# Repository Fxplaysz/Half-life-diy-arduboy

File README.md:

# Half-life-diy-arduboy
Hello everyone, this is my repository for my diy arduboy. Here you'll find the pcb and the 3d models later on.
I have made this DIY arduboy because i like mini handheld game consoles and electronics. This DIY Arduboy is very easy to build and can be made by anyone easily.

Aruduboy is a open source game console made by Kevin Bates. He has opensourced his console and made it easier for anyone to build it and have fun with it. I remember a few years back i tried making it by myself but i failed in doing so because of the technicalities in building it. So i've decided to make this project to let anyone make a DIY Arduboy easily and have fun while doing it.

It was made using KiCad and with the help of the internet. 
I made it in 2 days in the span of 5 hours in the 2 days.

# Features
* 0.96 SPI OLED display
* ISP pins for easy programming
* Buzzer for audio
* Flash chip to store more then 500+ games
* RGB LED
* *Silent* SMD push button switches. Good for long term gaming.

# Instructions
* Flash [Arduboy bootloader](https://github.com/MrBlinky/Arduboy-homemade-package) using the ISP header and a [usb asp](https://robu.in/product/usbasp-avr-programming-device-for-atmel-proccessors/)
* Upload games using the cart builder from MrBlinky [Arduboy-Python-Utilities](https://github.com/MrBlinky/Arduboy-Python-Utilities)
* Start Playing with it!

  - *More detailed instructions will be uploaded later*
    
# Photos
These are some of the photos of my PCBs.
1) PCB with smd mounted flash chip.
- Front

<details>
  <summary>Click to view front with components</summary>
  
</details>

- Back

<details>
  <summary>Click to view back with components</summary>
  
</details>

* PCB Lay out

2) PCB with support for flash module.
- Front

<details>
  <summary>Click to view front with components</summary>
  
</details>

- Back

<details>
  <summary>Click to view back with components</summary>

</details>

* PCB Lay out

* Schematics
   - [DIY Arduboy with Flash Module support](https://github.com/Fxplaysz/Half-life-diy-arduboy/blob/main/diy_ardubo_flash_module.pdf)
   - [DIY Arduboy with SMD flash chip](https://github.com/Fxplaysz/Half-life-diy-arduboy/blob/main/diy_ardubo_flash_module.pdf)

The flash module version supports the addition of a flash module instead of using smd flash chip. Its mainly through hole components making it easier to build and use it.

The SMD version is a little slimmer then the flash module version but its hard to solder without hot air gun. So the choice is yours to build. 

Anyone Interested in building it can check my [BOM list](https://github.com/Fxplaysz/Half-life-diy-arduboy/blob/main/BOM.md). Feel free to ask questions.
Have fun everyone!

This is the BOM list 
# DIY arduboy – bill of materials

<!-- Generated by Half Life from project cmuv6l7gq0e3701smizq8m7ku. Edits here are overwritten on the next sync. -->
<!-- Generated: 2026-10-10T20:20:58.583Z -->

> [!NOTE]
> This parts list is mirrored from [Half Life](https://halflife.hackclub.com). Editing it here will not change the platform's copy, and the next sync overwrites this file.

| Week | Tier | Parts funding |
| --- | --- | --- |
| Week 1 | Tier 2 | $65.00 |

| Part | What it's for | Qty | Unit | Total | Vendor |
| --- | --- | --- | --- | --- | --- |
| [Female header pins](https://robu.in/product/fh2-54-09-10pzd-xunpu-plugin1x10-pin-2-54mm-female-headers-rohs/) | To connect the oled display and arduino pro micro with the components. | 5 | $0.20 | $1.00 | [Robu.in](https://robu.in/product/fh2-54-09-10pzd-xunpu-plugin1x10-pin-2-54mm-female-headers-rohs/) |
| [SMD Tactile Switches](https://robu.in/product/1-month-warranty-1138/) | The buttons of my diy arduboy. | 20 | $0.12 | $2.40 | [Robu.in](https://robu.in/product/1-month-warranty-1138/) |
| [W25Q128 breakout flash chip module](https://robu.in/product/w25q128-large-capacity-flash-storage-module/) | The flash chip to hold the games of the flash module version of my DIY arduboy | 2 | $1.85 | $3.70 | [Robu.in](https://robu.in/product/w25q128-large-capacity-flash-storage-module/) |
| [USB ASP](https://robu.in/product/usbasp-avr-programming-device-for-atmel-proccessors/) | For programming and flashing the bootloader of the arduino pro micro | 1 | $2.06 | $2.06 | [Robu.in](https://robu.in/product/usbasp-avr-programming-device-for-atmel-proccessors/) |
| [Male header pins](https://robu.in/product/2-54mm-1x40-pin-male-single-row-straight-short-header-strip-pack-of-3/) | To make the pinouts for the battery connector and other connectors | 2 | $0.09 | $0.18 | [Robu.in](https://robu.in/product/2-54mm-1x40-pin-male-single-row-straight-short-header-strip-pack-of-3/) |
| [1k ohm resistor](https://quartzcomponents.com/products/1k-ohm-1-4-watt-resistor-with-1-tolerance-pack-of-10?variant=35648501383321&country=IN&currency=INR&utm_medium=product_sync&utm_source=google&utm_content=sag_organic&utm_campaign=sag_organic) | to make the cs driver chip (connecting resistor to bc557) | 1 | $0.10 | $0.10 | [quartzcomponents.com](https://quartzcomponents.com/products/1k-ohm-1-4-watt-resistor-with-1-tolerance-pack-of-10?variant=35648501383321&country=IN&currency=INR&utm_medium=product_sync&utm_source=google&utm_content=sag_organic&utm_campaign=sag_organic) |
| [5V boost module](https://robu.in/product/xl3608-boost-module-5v/) | To boost the voltage of the 3.7v batteries to power up my diy arduboy | 2 | $0.52 | $1.04 | [Robu.in](https://robu.in/product/xl3608-boost-module-5v/) |
| [Slide switch](https://robu.in/product/slide-switch-sk-17b/) | Slide switch to turn off or on the diy arduboy | 5 | $0.04 | $0.20 | [Robu.in](https://robu.in/product/slide-switch-sk-17b/) |
| [Passive buzzers](https://robu.in/product/1-month-warranty-1248/) | Buzzers to produce sound from my diy arduboy | 1 | $0.51 | $0.51 | [Robu.in](https://robu.in/product/1-month-warranty-1248/) |
| [Male to female jumper cables](https://robu.in/product/male-to-female-jumper-wires-40pcs-20cm/) | To debugg my diy arduboy | 1 | $0.51 | $0.51 | [Robu.in](https://robu.in/product/male-to-female-jumper-wires-40pcs-20cm/) |
| [AVR ISP 10 Pin to 6 Pin Adapter Board](https://robu.in/product/avr-isp-10-pin-to-6-pin-adapter-board/) | Adapter for flashing the bootloader and programming | 1 | $0.30 | $0.30 | [Robu.in](https://robu.in/product/avr-isp-10-pin-to-6-pin-adapter-board/) |
| [24AWG Single core teflon wire](https://robu.in/product/24awg-single-core-teflon-wire-red/) | For connecting passive components like the battery with the booster | 3 | $0.14 | $0.42 | [Robu.in](https://robu.in/product/24awg-single-core-teflon-wire-red/) |
| [ArduboyFlashChipSMD](https://robu-prod-media.s3.ap-south-1.amazonaws.com/PCB/pcb_6aca6d7ae1b39_gerber_file.zip) | SMD pcb version of my diy arduino | 5 | $1.86 | $9.30 | [Robu.in](https://robu-prod-media.s3.ap-south-1.amazonaws.com/PCB/pcb_6aca6d7ae1b39_gerber_file.zip) |
| [DiyArduboyFlashModule](https://robu-prod-media.s3.ap-south-1.amazonaws.com/PCB/pcb_6aca6de32484f_gerber_file.zip) | Another version of My DIY arduboy which can be used using a flash module instead of smd soldering | 5 | $1.86 | $9.30 | [Robu.in](https://robu-prod-media.s3.ap-south-1.amazonaws.com/PCB/pcb_6aca6de32484f_gerber_file.zip) |
| [Adafruit QSPI DIP Breakout Board - W25Q128](https://evelta.com/adafruit-qspi-dip-breakout-board---w25q128---128-mbit-16-mbyte---w25q128jvssiq/) | To test the smd version of DIY Arduboy | 2 | $4.45 | $8.90 | [evelta.com](https://evelta.com/adafruit-qspi-dip-breakout-board---w25q128---128-mbit-16-mbyte---w25q128jvssiq/) |
| [0.96 OLED Display Module](https://robu.in/product/0-96-oled-display-module-spi-i2c-128x64-7-pin-blue/) | The main display of My diy arduboy. I'll display the  games | 2 | $2.47 | $4.94 | [Robu.in](https://robu.in/product/0-96-oled-display-module-spi-i2c-128x64-7-pin-blue/) |
| [10k resistor](https://robu.in/product/mfr-25frf52-10k-yageo-metal-film-resistors-10k%cf%89-250mw-%c2%b1100ppm-%e2%84%83-%c2%b11-plugind2-4xl6-3mm-through-hole-resistors-rohs/) | To protect the cs pin from 5v voltage | 5 | $0.03 | $0.15 | [Robu.in](https://robu.in/product/mfr-25frf52-10k-yageo-metal-film-resistors-10k%cf%89-250mw-%c2%b1100ppm-%e2%84%83-%c2%b11-plugind2-4xl6-3mm-through-hole-resistors-rohs/) |
| [BC557 Transistor](https://robu.in/product/bc557-pnp-transistor-pack-of-20/) | To build the cs driver of my DIY arduboy | 12 | $0.02 | $0.24 | [Robu.in](https://robu.in/product/bc557-pnp-transistor-pack-of-20/) |
| [100nf capacitor](https://robu.in/product/100nf-50v-disc-capacitor/) | To smooth out and protect from voltage spike to the  flash chip | 11 | $0.01 | $0.11 | [Robu.in](https://robu.in/product/100nf-50v-disc-capacitor/) |
| [RGB SMD LED](https://robu.in/product/1-month-warranty-186/) | To display colour lights for my DIY Arduboy | 5 | $0.05 | $0.25 | [Robu.in](https://robu.in/product/1-month-warranty-186/) |
| [Arduino Pro Micro](https://robu.in/product/pro-micro-type-c-microcontroller-development-board-for-arduino/) | its the main microcontroller of my DIY Arduboy. and its responsible for running my DIY Arduboy | 2 | $5.57 | $11.14 | [Robu.in](https://robu.in/product/pro-micro-type-c-microcontroller-development-board-for-arduino/) |
| **Parts subtotal** | — | — | — | **$56.75** | — |
| **Tax & shipping** | — | — | — | **$2.53** | — |
| **Total** | — | — | — | **$59.28** | — |

$5.72 left of the tier's funding.

**Firmware Credit:** The test firmware used for this project is [Back to the Jungle](https://github.com/eried/ArduboyBackToTheJungle) created by **eried**.

* **Arduboy community:** https://community.arduboy.com/

* **Arduboy:** https://www.arduboy.com/

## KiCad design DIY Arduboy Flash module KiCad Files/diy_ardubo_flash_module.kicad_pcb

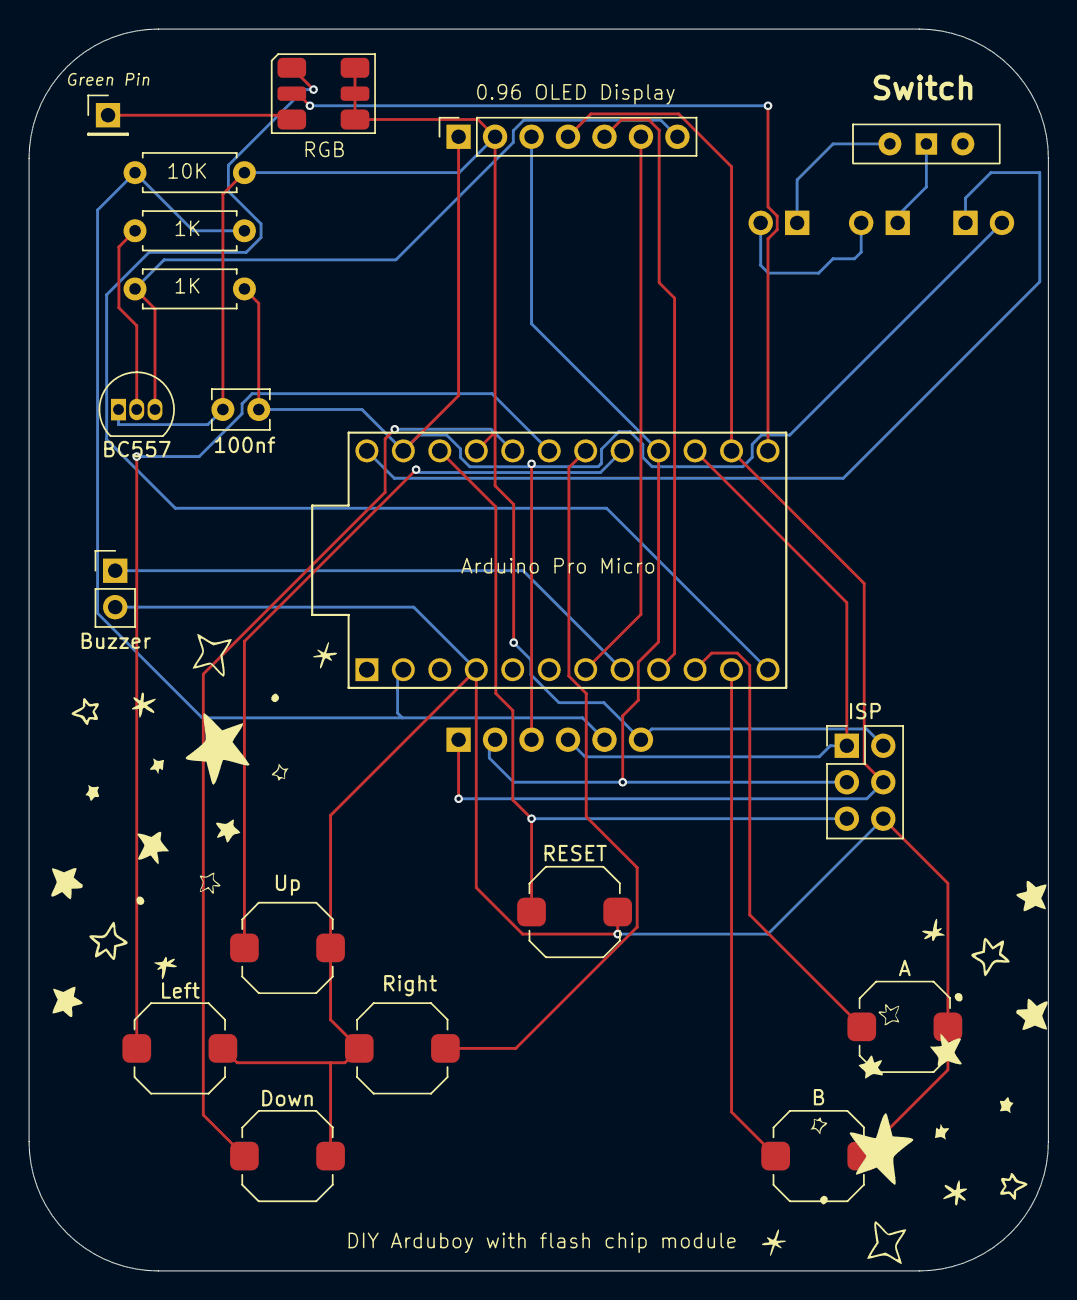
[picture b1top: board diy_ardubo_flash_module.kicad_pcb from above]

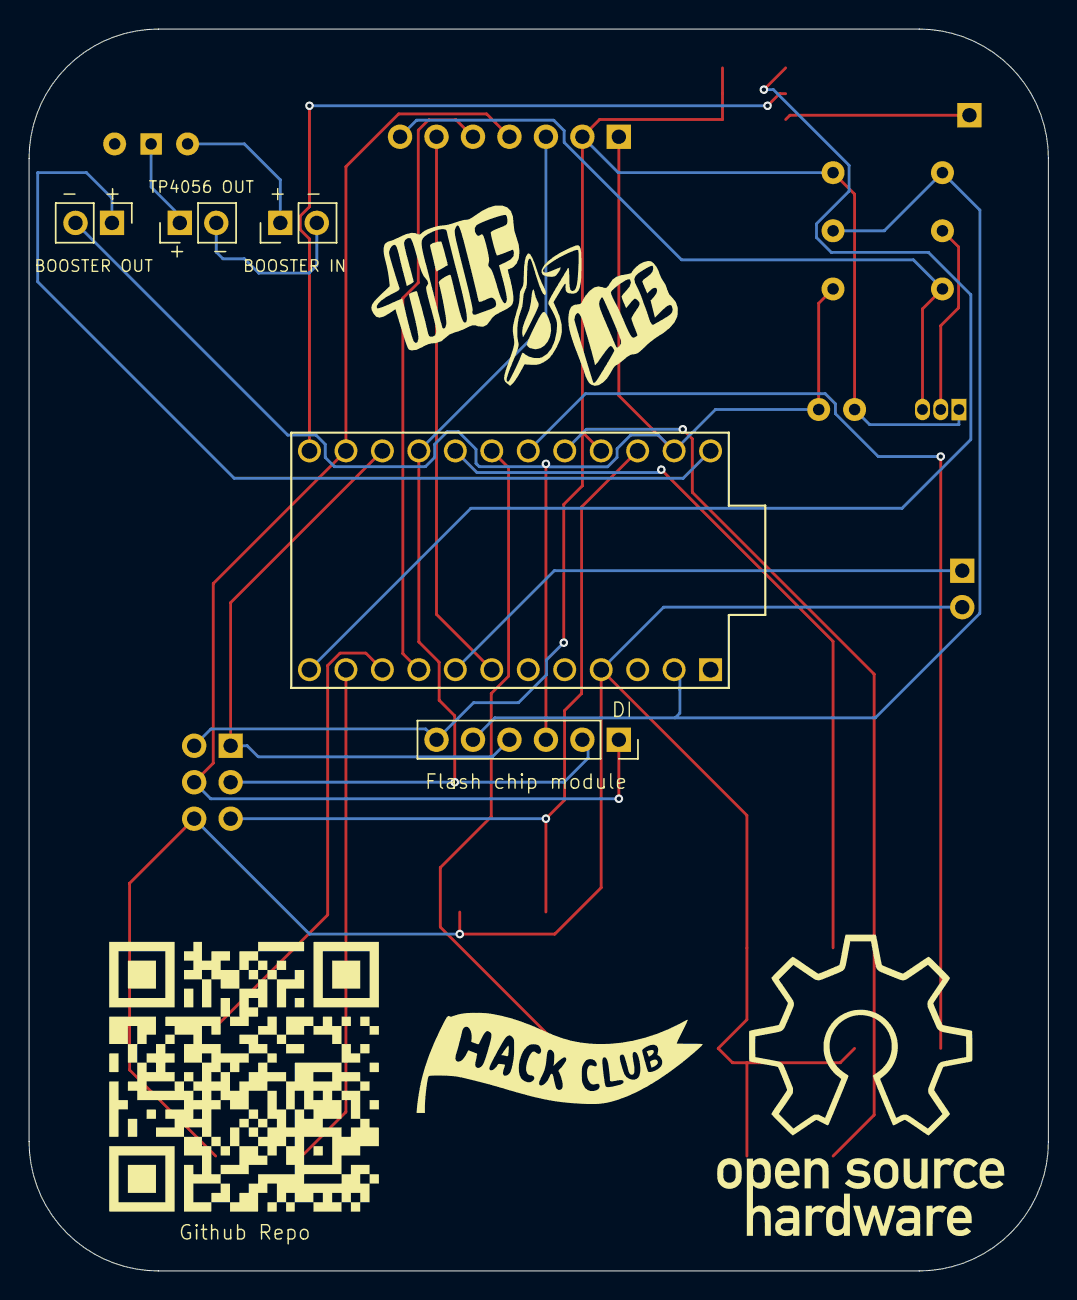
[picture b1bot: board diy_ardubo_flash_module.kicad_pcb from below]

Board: 2 copper layers, 71.0 x 86.5 mm, 23 parts (4 on the bottom side), 26 nets.

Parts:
100nf: C; C_Disc_D3.8mm_W2.6mm_P2.50mm
A: SW_Push; SW_Push_1TS009xxxx-xxxx-xxxx_6x6x5mm
B: SW_Push; SW_Push_1TS009xxxx-xxxx-xxxx_6x6x5mm
BOOSTER IN: Conn_01x02_Pin; PinHeader_1x02_P2.54mm_Vertical
BOOSTER OUT: Conn_01x02_Pin; PinHeader_1x02_P2.54mm_Vertical
BZ1: Buzzer; PinHeader_1x02_P2.54mm_Vertical
D1: Inolux_IN-P55TATRGB; LED_Inolux_IN-P55TATRGB_PLCC6_5.0x5.5mm_P1.8mm
Down: SW_Push; SW_Push_1TS009xxxx-xxxx-xxxx_6x6x5mm
ISP: Conn_02x03_Odd_Even; PinHeader_2x03_P2.54mm_Vertical
J2: Conn_01x07_Pin; PinSocket_1x07_P2.54mm_Vertical
J4: Conn_01x06_Pin; PinSocket_1x06_P2.54mm_Vertical
J5: Conn_01x01_Pin; PinHeader_1x01_P2.54mm_Vertical
Q1: BC557; TO-92_Inline
R1, R2, R3: R; R_Axial_DIN0207_L6.3mm_D2.5mm_P7.62mm_Horizontal
RESET: SW_Push; SW_Push_1TS009xxxx-xxxx-xxxx_6x6x5mm
SW3, SW4: SW_Push; SW_Push_1TS009xxxx-xxxx-xxxx_6x6x5mm
SW8: SW_SPDT; SW_Slide-03_Wuerth-WS-SLTV_10x2.5x6.4_P2.54mm
TP4056 OUT: Conn_01x02_Pin; PinHeader_1x02_P2.54mm_Vertical
U1: ProMicro
Up: SW_Push; SW_Push_1TS009xxxx-xxxx-xxxx_6x6x5mm

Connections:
unnamed: BZ1.1 (+), U1.8 (C6)
unnamed: A.2, B.2, BZ1.2 (-), Down.2, ISP.6, RESET.2, SW3.2, SW4.1, U1.4 (GND), Up.2
unnamed: 100nf.1, D1.4 (AG), D1.5 (AR), D1.6 (AB), ISP.2, J2.2 (VCC), J4.6, Q1.1 (C), R1.2, U1.21 (VCC)
unnamed: D1.1 (KB), U1.12 (B5)
unnamed: D1.3 (KG), J5.1 (Pin_1_1)
unnamed: D1.2 (KR), U1.13 (B6)
unnamed: SW8.1 (A), TP4056 OUT.1
unnamed: BOOSTER IN.2, TP4056 OUT.2
unnamed: J2.7 (CS), Q1.3 (E), R3.1
unnamed: ISP.3, J2.3 (D0), J4.2, U1.16 (B1)
unnamed: ISP.4, J2.4 (D1), J4.1, U1.14 (B2)
unnamed: J2.6 (DC), U1.7 (D4)
unnamed: 100nf.2, BOOSTER OUT.2, J2.1 (GND), J4.3, R3.2, U1.23 (GND)
unnamed: J2.5 (RES), U1.9 (D7)
unnamed: ISP.1, J4.4, U1.15 (B3)
unnamed: ISP.5, RESET.1, U1.22 (RST)
unnamed: J4.5, R1.1, R2.2, U1.2 (RX)
unnamed: BOOSTER IN.1, SW8.2 (B)
unnamed: BOOSTER OUT.1, U1.24 (RAW)
unnamed: Q1.2 (B), R2.1
unnamed: B.1, U1.11 (B4)
unnamed: A.1, U1.10 (E6)
unnamed: Down.1, U1.20 (F4)
unnamed: SW3.1, U1.19 (F5)
unnamed: SW4.2, U1.18 (F6)
unnamed: U1.17 (F7), Up.1

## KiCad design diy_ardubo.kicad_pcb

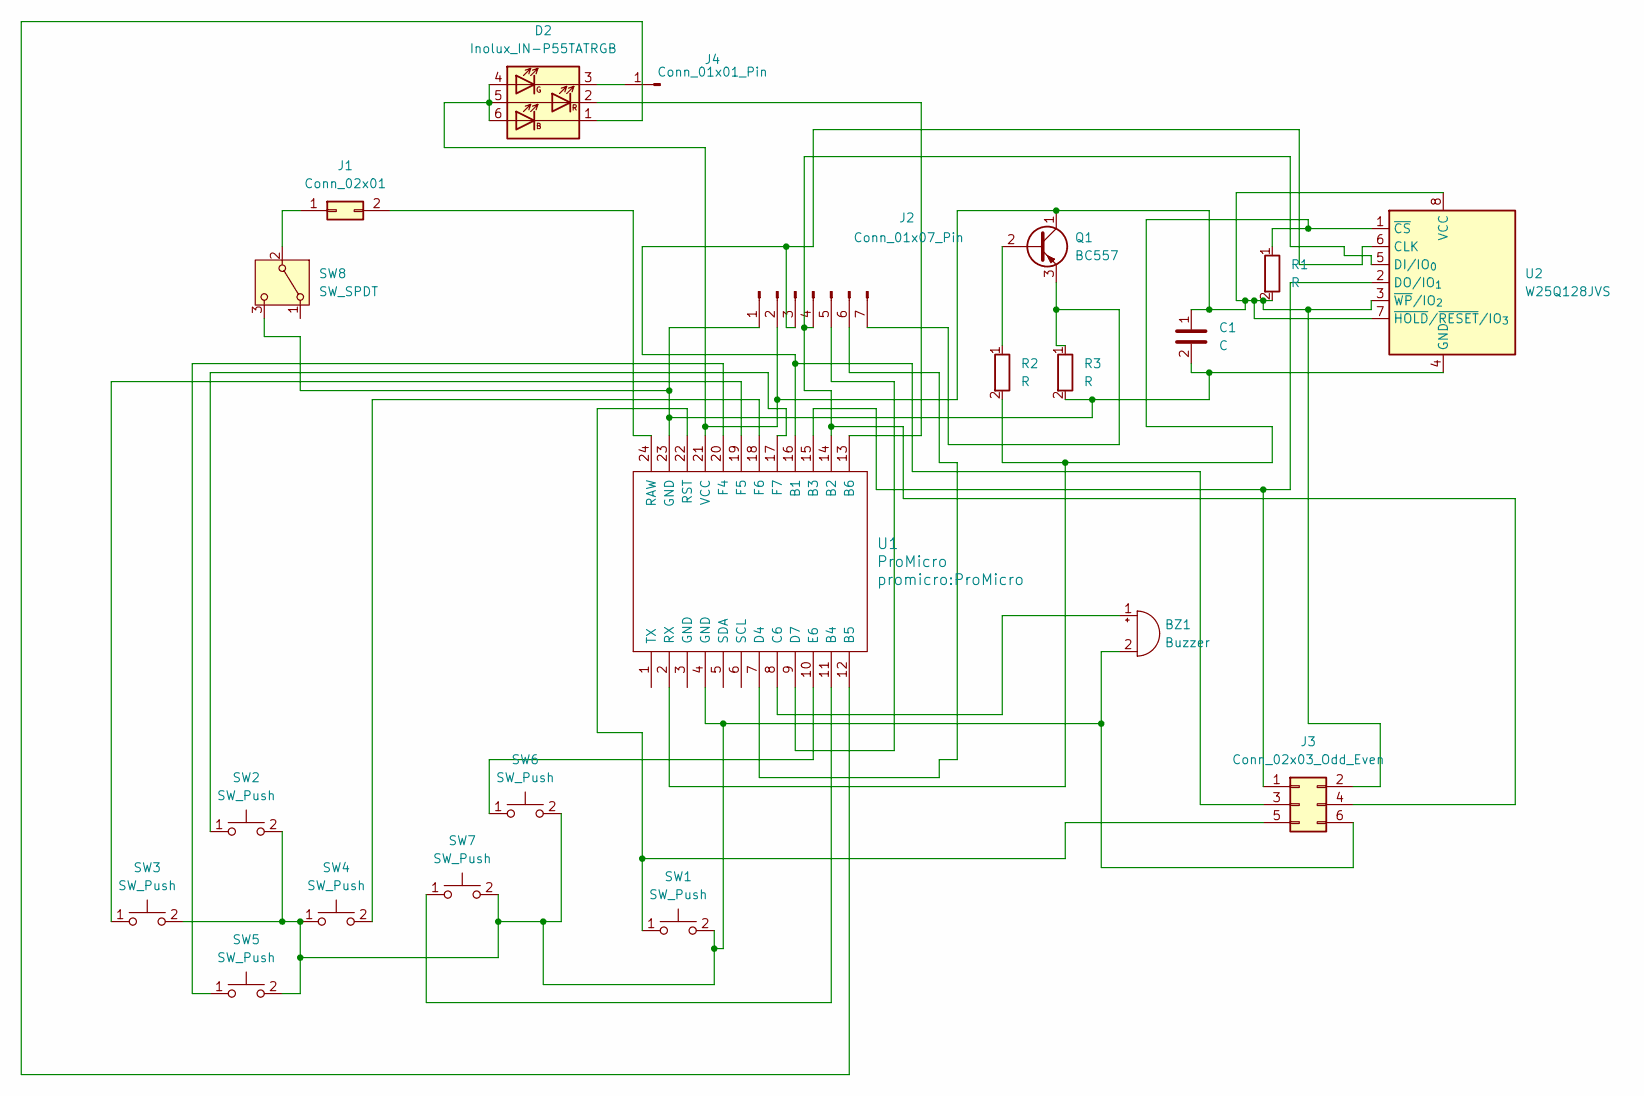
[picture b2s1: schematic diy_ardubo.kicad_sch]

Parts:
BZ1: Buzzer; PinHeader_1x02_P2.54mm_Vertical
C1: C; C_Disc_D3.8mm_W2.6mm_P2.50mm
D2: Inolux_IN-P55TATRGB; LED_Inolux_IN-P55TATRGB_PLCC6_5.0x5.5mm_P1.8mm
J1: Conn_02x01; PinHeader_2x01_P2.54mm_Vertical
J2: Conn_01x07_Pin; PinSocket_1x07_P2.54mm_Vertical
J3: Conn_02x03_Odd_Even; PinHeader_2x03_P2.54mm_Vertical
J4: Conn_01x01_Pin; PinHeader_1x01_P2.54mm_Vertical
Q1: BC557; TO-92_Inline
R1, R2, R3: R; R_Axial_DIN0207_L6.3mm_D2.5mm_P7.62mm_Horizontal
SW1, SW2, SW3, SW4, SW5, SW6, SW7: SW_Push; SW_Push_1TS009xxxx-xxxx-xxxx_6x6x5mm
SW8: SW_SPDT; SW_Slide-03_Wuerth-WS-SLTV_10x2.5x6.4_P2.54mm
U1: ProMicro
U2: W25Q128JVS; SOIC-8_5.3x5.3mm_P1.27mm

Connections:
unnamed: BZ1.1 (+), U1.8 (C6)
unnamed: BZ1.2 (-), J3.6, SW1.2, SW2.2, SW3.2, SW4.1, SW5.2, SW6.2, SW7.2, U1.4 (GND)
unnamed: C1.1, D2.4 (AG), D2.5 (AR), D2.6 (AB), J2.2 (VCC), J3.2, Q1.1 (C), R1.2, U1.21 (VCC), U2.3 (~WP/IO_{2}), U2.7 (~HOLD/~RESET/IO_{3}), U2.8 (VCC)
unnamed: D2.1 (KB), U1.12 (B5)
unnamed: D2.3 (KG), J4.1 (Pin_1_1)
unnamed: D2.2 (KR), U1.13 (B6)
unnamed: J1.1, SW8.2 (B)
unnamed: J1.2, U1.24 (RAW)
unnamed: J2.7 (CS), Q1.3 (E), R3.1
unnamed: J2.3 (D0), J3.3, U1.16 (B1), U2.6 (CLK)
unnamed: J2.4 (D1), J3.4, U1.14 (B2), U2.5 (DI/IO_{0})
unnamed: J2.6 (DC), U1.7 (D4)
unnamed: C1.2, J2.1 (GND), R3.2, SW8.3 (C), U1.23 (GND), U2.4 (GND)
unnamed: J2.5 (RES), U1.9 (D7)
unnamed: J3.1, U1.15 (B3), U2.2 (DO/IO_{1})
unnamed: J3.5, SW1.1, U1.22 (RST)
unnamed: Q1.2 (B), R2.1
unnamed: SW7.1, U1.11 (B4)
unnamed: SW6.1, U1.10 (E6)
unnamed: SW5.1, U1.20 (F4)
unnamed: SW3.1, U1.19 (F5)
unnamed: SW4.2, U1.18 (F6)
unnamed: SW2.1, U1.17 (F7)
unnamed: R1.1, R2.2, U1.2 (RX), U2.1 (~CS)

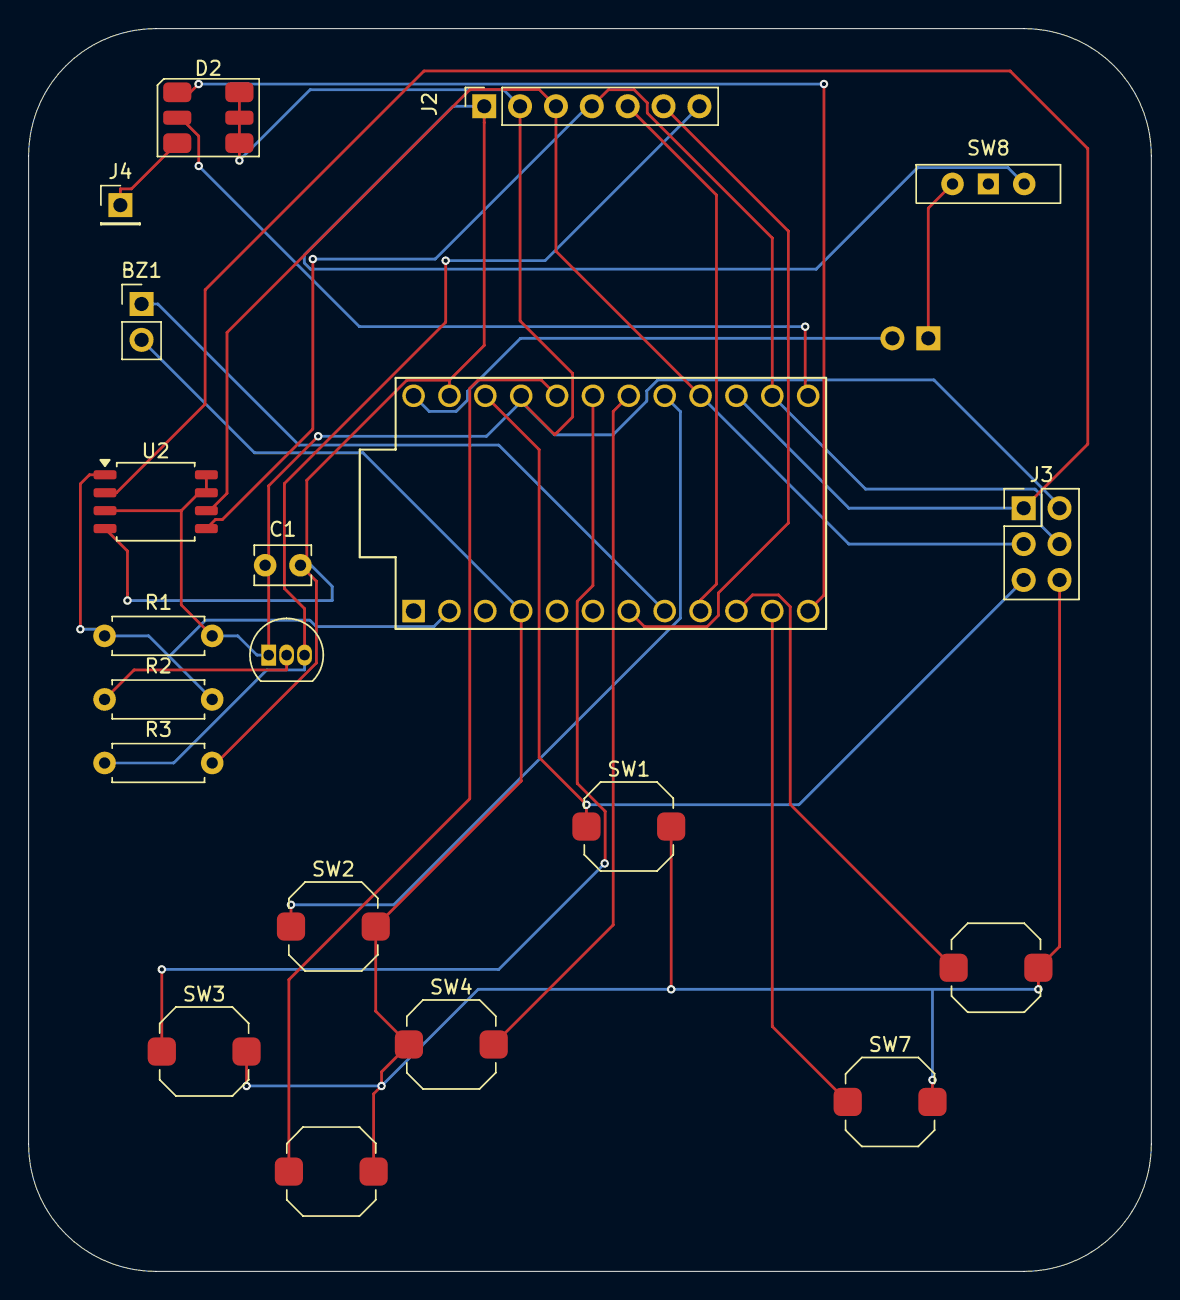
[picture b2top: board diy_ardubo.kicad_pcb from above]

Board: 2 copper layers, 79.5 x 88.0 mm, 21 parts (1 on the bottom side), 24 nets.
